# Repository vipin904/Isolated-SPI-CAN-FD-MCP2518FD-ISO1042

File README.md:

# Isolated-SPI-CAN-FD-MCP2518FD-ISO1042
Open-source galvanically isolated SPI-to-CAN FD module based on Microchip MCP2518FD CAN FD controller and Texas Instruments ISO1042 isolated CAN transceiver.
Isolated SPI-to-CAN FD Module
The module provides a practical solution for adding a reliable, isolated CAN/CAN FD interface to microcontrollers that have an available SPI interface but do not have an integrated CAN FD peripheral.

Features

- Single CAN FD channel
- Galvanic isolation
- SPI interface
- MCP2518FD CAN FD controller
- ISO1042 isolated CAN transceiver
- Supports Classical CAN (CAN 2.0B)
- Supports CAN FD
- CAN arbitration bit rate up to 1 Mbps
- CAN FD data bit rate up to 5 Mbps with ISO1042
- ±70 V DC CAN bus fault protection
- ±16 kV HBM ESD tolerance on CAN bus pins
- ±30 V common-mode voltage range
- Driver Dominant Time-Out (TXD DTO)
- High-impedance passive CAN bus terminals when unpowered
- Compact PCB design

Main Components

MCP2518FD – CAN FD Controller

The MCP2518FD is a CAN FD controller that communicates with the host microcontroller through an SPI interface.

Key capabilities:

- Classical CAN 2.0B support
- CAN FD support
- Arbitration bit rate up to 1 Mbps
- Data bit rate up to 8 Mbps
- 31 configurable FIFOs
- 32 flexible filter and mask objects
- ISO 11898-1:2015 compliant CAN protocol controller

ISO1042 – Isolated CAN Transceiver

The ISO1042 is a galvanically isolated CAN transceiver from Texas Instruments.

Key features:

- ISO 11898-2:2016 physical-layer compliance
- Classical CAN up to 1 Mbps
- CAN FD support
- CAN FD data rate up to 5 Mbps
- Low loop delay
- ±70 V bus fault protection
- ±16 kV HBM ESD protection on CAN bus pins
- ±30 V common-mode voltage range
- TXD dominant-state time-out protection

Block Diagram

             ┌──────────────────────┐
             │   Host Microcontroller│
             │                      │
             │      SPI Interface   │
             └──────────┬───────────┘
                        │
                        │ SPI
                        ▼
             ┌──────────────────────┐
             │      MCP2518FD       │
             │     CAN FD Controller│
             └──────────┬───────────┘
                        │
                        │ CAN TX/RX
                        ▼
             ┌──────────────────────┐
             │       ISO1042        │
             │ Isolated CAN Transceiver│
             └──────────┬───────────┘
                        │
                  Galvanic Isolation
                        │
                        ▼
                  ┌────────────┐
                  │  CAN Bus   │
                  │ CANH/CANL  │
                  └────────────┘

Applications

This module can be used for:

- Industrial automation
- Embedded systems
- Automotive electronics
- EV and charging applications
- Battery management systems
- Motor controllers
- Power electronics
- Industrial communication
- Data acquisition systems
- Microcontrollers without an integrated CAN FD peripheral

Repository Contents

Isolated-SPI-CAN-FD/
│
├── Hardware/
│   ├── Schematic/
│   ├── PCB/
│   ├── Gerber/
│   ├── BOM/
│   └── Manufacturing/
│
├── Documentation/
│   ├── Datasheets/
│   └── Design_Notes/
│
├── Images/
│   ├── Schematic.png
│   ├── PCB_3D.png
│   └── Board_Top.png
│
├── LICENSE
└── README.md

Design Information

Parameter| Specification
CAN Channels| 1
CAN Controller| MCP2518FD
CAN Transceiver| ISO1042
Host Interface| SPI
Isolation| Galvanic
Classical CAN| Supported
CAN FD| Supported
Arbitration Rate| Up to 1 Mbps
CAN FD Data Rate| Up to 5 Mbps with ISO1042
Bus Fault Protection| ±70 V
Bus ESD Protection| ±16 kV HBM
Common-Mode Range| ±30 V

PCB Design

The PCB has been designed with focus on:

- Compact form factor
- Proper isolation between logic and CAN domains
- CAN signal integrity
- Short high-speed signal paths
- Appropriate power decoupling
- Practical manufacturing considerations
- CAN bus termination provisions

Hardware Files

The repository includes the available hardware design files:

- Schematic
- PCB layout
- Gerber files
- Bill of Materials (BOM)
- Manufacturing files
- Design documentation

Open Source

This project is shared as an open-source hardware design for learning, experimentation, prototyping and further development.

You are welcome to:

- Study the design
- Build the hardware
- Modify the design
- Improve the design
- Use it as a reference for your own CAN/CAN FD projects

Please review the component datasheets and validate the design for your specific application before using it in a production or safety-critical system.

Disclaimer

This project is provided for educational, development and prototyping purposes. The design has not been certified for any specific automotive, industrial or safety-critical application.

Users are responsible for validating electrical performance, EMC/EMI compliance, thermal performance, isolation requirements and applicable regulatory requirements for their intended application.

References

- Microchip MCP2518FD CAN FD Controller Datasheet
- Texas Instruments ISO1042 Isolated CAN Transceiver Datasheet
- ISO 11898-1 – CAN Data Link Layer and Physical Signalling
- ISO 11898-2 – High-Speed CAN Physical Layer

Author

Vipin Dhariwal

PCB Design | Embedded Hardware | Electronics | CAN/CAN FD

---

⭐ If you find this project useful, consider starring the repository and sharing your feedback.

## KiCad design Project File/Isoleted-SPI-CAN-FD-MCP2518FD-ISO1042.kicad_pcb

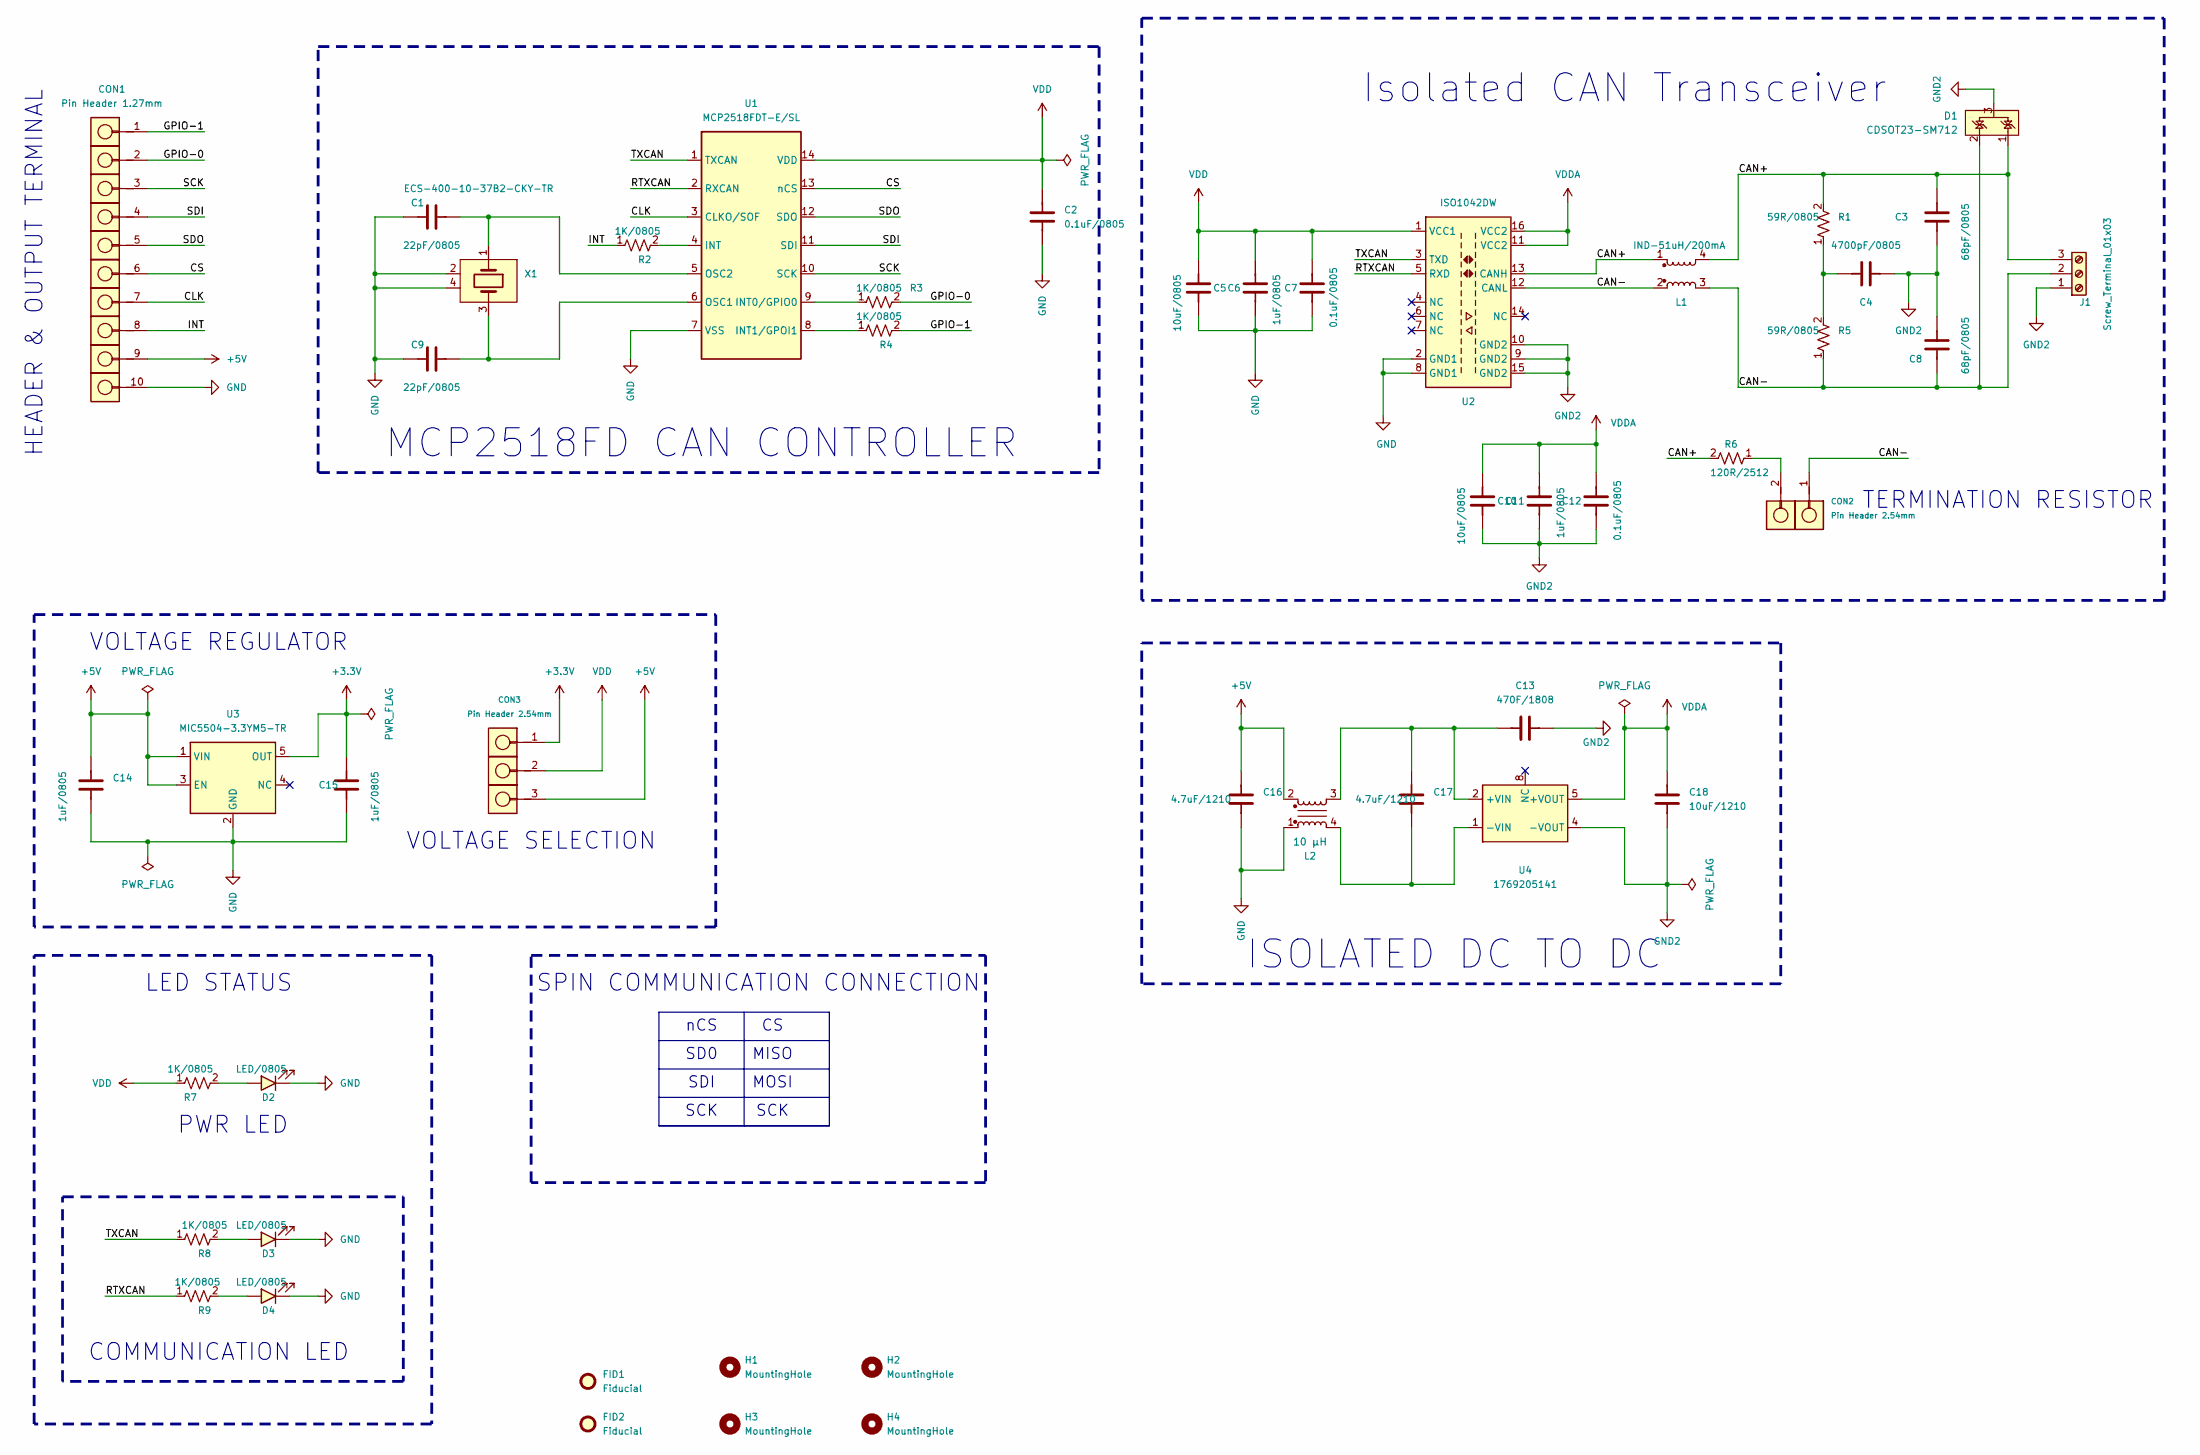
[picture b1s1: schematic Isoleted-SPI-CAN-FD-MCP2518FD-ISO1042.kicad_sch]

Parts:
C1, C9: 22pF/0805; Cap 0805; Part Number VJ0805A220JXGAT5Z
C2, C7, C12: 0.1uF/0805; Cap 0805; Part Number C0805Y104J3RACTU
C3, C8: 68pF/0805; Cap 0805; Part Number VJ0805A680JXBMC
C4: 4700pF/0805; Cap 0805; Part Number VJ0402Y472KLAAJ32
C5, C10: 10uF/0805; Cap 0805; Part Number GRM21BR6YA106KE43L
C6, C11, C14, C15: 1uF/0805; Cap 0805; Part Number VJ0805Y105KXARW1BC
C13: 470F/1808; Cap_1210_3225Metric_Pad1.33x2.70mm_HandSolder; Manufacturer Part No 885342210003
C16, C17: 4.7uF/1210; Cap_1210_3225Metric_Pad1.33x2.70mm_HandSolder; Manufacturer Part No 885012209013
C18: 10uF/1210; Cap_1210_3225Metric_Pad1.33x2.70mm_HandSolder; Manufacturer Part No 885012209014
CON1: Pin Header 1.27mm; PinHeader_1x10_P1.27mm_Vertical
CON2: Pin Header 2.54mm; Pin Header_1x02_P2.54mm_Vertical
CON3: Pin Header 2.54mm; PinHeader_1x03_P2.54mm_Vertical
D1: CDSOT23-SM712; SOT-23; Part Number CDSOT23-SM712
D2, D3, D4: LED/0805; LED_0805_2012Metric
FID1, FID2: Fiducial; Fiducial_0.5mm_Mask1mm
H1, H2, H3, H4: MountingHole
J1: Screw_Terminal_01x03; TerminalBlock_Phoenix_MPT-0,5-3-2.54_1x03_P2.54mm_Horizontal
L1: IND-51uH/200mA; IND_ACT45R_TDK; Part Number ACT45B-510-2P-TL003
L2: 74422x_744226S; IND-L_Wurth_WE-SL2-74422x; Part Number 744226S
R1, R5: 59R/0805; RES 0805; Part Number CRCW120659R0FKEA
R2, R3, R4, R7, R8, R9: 1K/0805; RES 0805
R6: 120R/2512; RES_2512_6332Metric_Pad1.40x3.35mm_HandSolder; Part Number CRCW2512120RFKEG
U1: MCP2518FDT-E/SL; SOIC-14; Manufacturer Part No MCP251863T-E/SS
U2: ISO1042DW; SOIC-16-Package_SOSOIC-16W_7.5x10.3mm_P1.27mm; Part Number ISO1042DW
U3: MIC5504-3.3YM5-TR; SOT-23-5; Manufacturer Part No MIC5504-3.3YM5-TR
U4: 1769205141; U_Wurth_WPME-FISM_SMT-8_1769205x41; Manufacturer Part No 1769205241
X1: ECS-400-10-37B2-CKY-TR; Crystal ECX-1637B2_ECS-M; Manufacturer Part No ECS-400-10-37B2-CKY-TR

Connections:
+3.3V: C15.2, CON3.1, U3.5 (OUT)
+5V: C14.2, C16.2, CON1.9, CON3.3, L2.2, U3.1 (VIN), U3.3 (EN)
/CAN+: C3.2, D1.1 (A1), J1.3, L1.1, L1.4, R1.2, R6.2, U2.13 (CANH)
/CAN-: C8.1, CON2.1, D1.2 (A1), J1.2, L1.2, L1.3, R5.1, U2.12 (CANL)
/CLK: CON1.7, U1.3 (CLKO/SOF)
/CS: CON1.6, U1.13 (nCS)
/GPIO-0: CON1.2, R3.2
/GPIO-1: CON1.1, R4.2
/INT: CON1.8, R2.1
/RTXCAN: R9.1, U1.2 (RXCAN), U2.5 (RXD)
/SCK: CON1.3, U1.10 (SCK)
/SDI: CON1.4, U1.11 (SDI)
/SDO: CON1.5, U1.12 (SDO)
/TXCAN: R8.1, U1.1 (TXCAN), U2.3 (TXD)
GND: C1.1, C2.1, C5.1, C6.1, C7.1, C9.1, C14.1, C15.1, C16.1, CON1.10, D2.2 (K), D3.2 (K), D4.2 (K), L2.1, U1.7 (VSS), U2.2 (GND1), U2.8 (GND1), U3.2 (GND), X1.2 (GND), X1.4 (GND)
GND2: C3.1, C4.2, C8.2, C10.1, C11.1, C12.1, C13.2, C18.1, D1.3 (A2), J1.1, U2.9 (GND2), U2.10 (GND2), U2.15 (GND2), U4.4 (-VOUT)
unnamed: C4.1, R1.1, R5.2
unnamed: CON2.2, R6.1
unnamed: D2.1 (A), R7.2
unnamed: D3.1 (A), R8.2
unnamed: D4.1 (A), R9.2
unnamed: R3.1, U1.9 (INT0/GPIO0)
unnamed: R4.1, U1.8 (INT1/GPOI1)
unnamed: R2.2, U1.4 (INT)
unnamed: C9.2, U1.6 (OSC1), X1.3 (OUT/IN)
unnamed: C1.2, U1.5 (OSC2), X1.1 (IN/OUT)
unnamed: C13.1, C17.2, L2.3, U4.2 (+VIN)
unnamed: C17.1, L2.4, U4.1 (-VIN)
VDD: C2.2, C5.2, C6.2, C7.2, CON3.2, R7.1, U1.14 (VDD), U2.1 (VCC1)
VDDA: C10.2, C11.2, C12.2, C18.2, U2.11 (VCC2), U2.16 (VCC2), U4.5 (+VOUT)

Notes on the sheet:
MOSI
COMMUNICATION LED
LED STATUS
HEADER & OUTPUT TERMINAL
SCK
MCP2518FD CAN CONTROLLER
TERMINATION RESISTOR
SDI
PWR LED
SPIN COMMUNICATION CONNECTION
ISOLATED DC TO DC
nCS
VOLTAGE SELECTION
Isolated CAN Transceiver
VOLTAGE REGULATOR
SD0
MISO

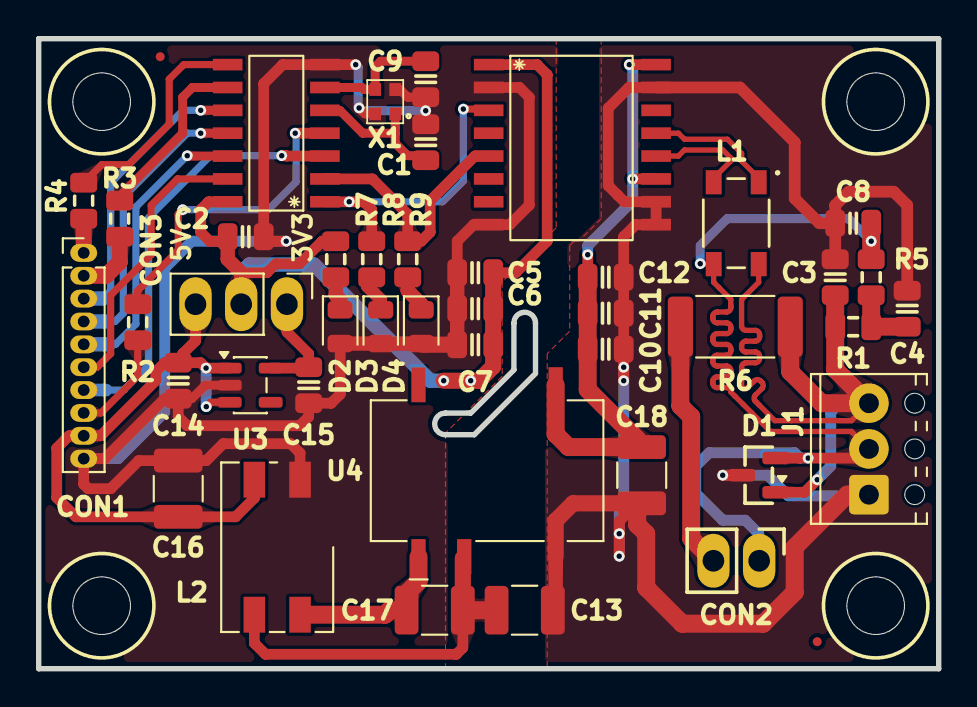
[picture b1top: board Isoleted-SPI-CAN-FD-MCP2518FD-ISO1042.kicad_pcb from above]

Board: 2 copper layers, 50.0 x 35.0 mm, 44 parts (0 on the bottom side), 30 nets.
